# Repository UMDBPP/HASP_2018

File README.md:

# HASP_2018
2018 HASP payload with microphones and a dropped module.

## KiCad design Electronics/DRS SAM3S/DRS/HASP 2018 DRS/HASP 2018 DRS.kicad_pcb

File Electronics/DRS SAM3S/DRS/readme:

This repository contains the KiCad schematic for the HASP2018 DRS.
In the folder you will find the .sch file that contains the schematic, the .kicad_pcb file with the pcb layout file, 
the custom.lib library for the schematic components, and the customfoots.pretty folder with the pcb layout components.

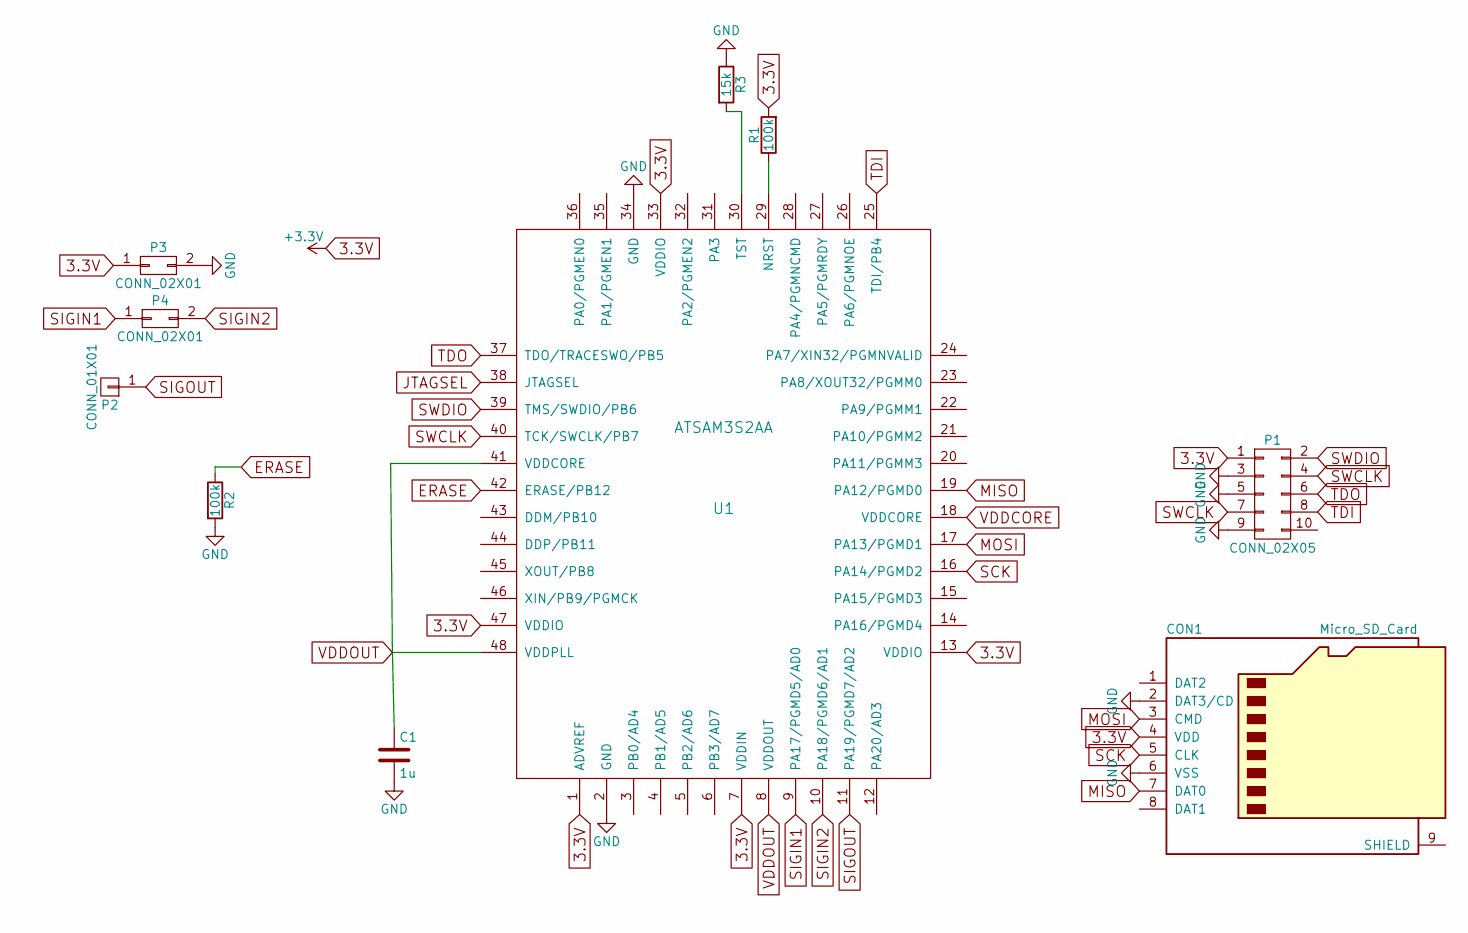
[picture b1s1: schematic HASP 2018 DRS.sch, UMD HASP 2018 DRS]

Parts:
C1: 1u; C_0603
CON1: Micro_SD_Card; MicroSd_Wurth_693072010801
P1: CONN_02X05; Pin_Header_Straight_2x05_Pitch1.27mm
P2: CONN_01X01; Pin_Header_Straight_1x01_Pitch1.27mm
P3, P4: CONN_02X01; Pin_Header_Straight_1x02_Pitch1.27mm
R1, R2: 100k; R_0603
R3: 15k; R_0603
U1: ATSAM3S2AA; QFP50P900X900X160-48N

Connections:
3.3V: CON1.4 (VDD), P1.1, P3.1, R1.2, U1.1 (ADVREF), U1.7 (VDDIN), U1.13 (VDDIO), U1.33 (VDDIO), U1.47 (VDDIO)
ERASE: R2.1, U1.42 (ERASE/PB12)
GND: C1.2, CON1.2 (DAT3/CD), CON1.6 (VSS), P1.3, P1.5, P1.9, P3.2, R2.2, R3.1, U1.2 (GND), U1.34 (GND)
JTAGSEL: U1.38 (JTAGSEL)
MISO: CON1.7 (DAT0), U1.19 (PA12/PGMD0)
MOSI: CON1.3 (CMD), U1.17 (PA13/PGMD1)
unnamed: R1.1, U1.29 (NRST)
unnamed: R3.2, U1.30 (TST)
SCK: CON1.5 (CLK), U1.16 (PA14/PGMD2)
SIGIN1: P4.1, U1.9 (PA17/PGMD5/AD0)
SIGIN2: P4.2, U1.10 (PA18/PGMD6/AD1)
SIGOUT: P2.1, U1.11 (PA19/PGMD7/AD2)
SWCLK: P1.4, P1.7, U1.40 (TCK/SWCLK/PB7)
SWDIO: P1.2, U1.39 (TMS/SWDIO/PB6)
TDI: P1.8, U1.25 (TDI/PB4)
TDO: P1.6, U1.37 (TDO/TRACESWO/PB5)
VDDCORE: U1.18 (VDDCORE)
VDDOUT: C1.1, U1.8 (VDDOUT), U1.41 (VDDCORE), U1.48 (VDDPLL)

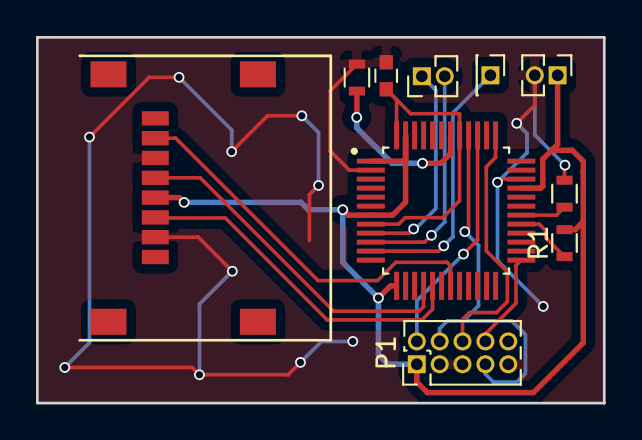
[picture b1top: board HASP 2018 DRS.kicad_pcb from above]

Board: 2 copper layers, 31.5 x 20.3 mm, 10 parts (0 on the bottom side), 16 nets.

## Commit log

2017-12-15 Initial CAD
2017-12-16 updated cad
2018-04-11 Initial Relay Board Schematic
2018-04-20 fixed rev 1 drs
2018-05-04 Relay Board
2018-05-07 gerbers
2018-05-30 new stuff
2018-06-11 Add files via upload
    Screw holes are a little offset, and need to add modifications to attach the drop mod to the actuator plate
2018-06-12 Add files via upload
    Adjustments made to drop box.
    Drill holes added to the upper plate.
    U-bolts and corresponding nuts added to drawing.
    Note: Heavy Gauge wire may suffice in place of a U-bolt and nut
2018-07-05 SAMD21 DRS
2018-07-08 Create New Relay Board
2018-07-08 last year's flight code
2018-07-09 I routed a board, and it's really tiny
2018-07-10 got rid of unnecessary things on relay board, fixed the SD card routing, set up rough pass of board size
2018-07-11 rerouted relay board, also put the power regulator in this repo from last years
2018-07-14 added drs fsw
2018-07-20 change write to write string instead of bytes. Also added flush
2018-07-22 uno code
2018-07-22 added das status message
2018-07-22 hcanges to serial code
2018-07-23 minor changes
2018-07-26 Add files via upload
    The version of Uno software from integration. Changes include refactored command handling and a new format for the downlink.
2018-07-26 Add files via upload
    Integration version of the nano software. Accounts for changes made to our discrete signaling and detection timing.
2018-07-28 software to check the HASP website and pull down new telemetry packets
2018-07-28 Added query to get payload number
2018-08-10 Working DRS code on an Arduino Nano
2018-08-11 added RNG voltage output for DRS interface
2018-08-12 HAAT arduino code with working DRS implementation
2018-08-15 changed flight serial baud back to 1200
2018-08-31 rewrote telem_parser script in python to make it better
2018-08-31 Updated to handle grabbing last few lines in previous file when a new file is created
2018-08-31 Added filewriting functionality
2018-08-31 fixed bug for first grab of telemetry
